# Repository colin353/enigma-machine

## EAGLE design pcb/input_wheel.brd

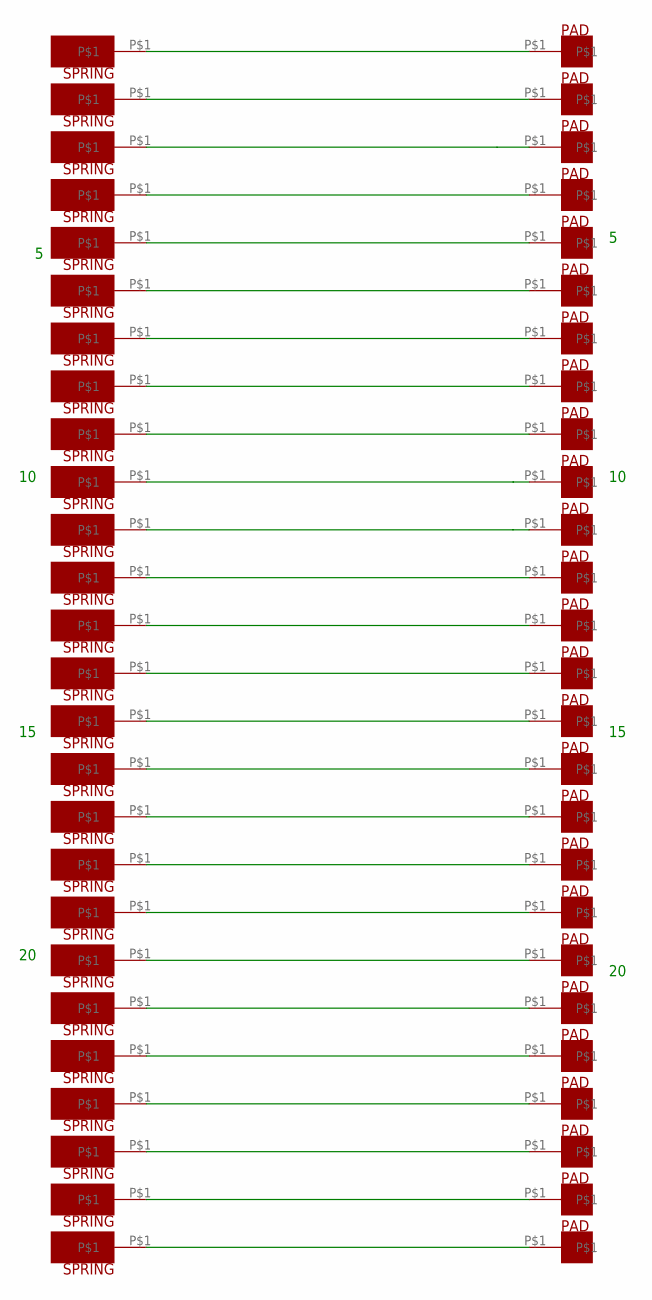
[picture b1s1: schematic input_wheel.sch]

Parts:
U$1, U$2, U$3, U$4, U$5, U$6, U$7, U$8, U$9, U$10, U$11, U$12, U$13, U$14, U$15, U$16, U$17, U$18, U$19, U$20, U$21, U$22, U$23, U$24, U$25, U$26: CONTACT
U$27, U$28, U$29, U$30, U$31, U$32, U$33, U$34, U$35, U$36, U$37, U$38, U$39, U$40, U$41, U$42, U$43, U$44, U$45, U$46, U$47, U$48, U$49, U$50, U$51, U$52: SPRING

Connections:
unnamed: U$10.P$1, U$36.P$1
unnamed: U$1.P$1, U$27.P$1
unnamed: U$2.P$1, U$28.P$1
unnamed: U$4.P$1, U$30.P$1
unnamed: U$11.P$1, U$37.P$1
unnamed: U$5.P$1, U$31.P$1
unnamed: U$6.P$1, U$32.P$1
unnamed: U$7.P$1, U$33.P$1
unnamed: U$8.P$1, U$34.P$1
unnamed: U$9.P$1, U$35.P$1
unnamed: U$12.P$1, U$38.P$1
unnamed: U$13.P$1, U$39.P$1
unnamed: U$14.P$1, U$40.P$1
unnamed: U$15.P$1, U$41.P$1
unnamed: U$16.P$1, U$42.P$1
unnamed: U$17.P$1, U$43.P$1
unnamed: U$18.P$1, U$44.P$1
unnamed: U$19.P$1, U$45.P$1
unnamed: U$20.P$1, U$46.P$1
unnamed: U$21.P$1, U$47.P$1
unnamed: U$22.P$1, U$48.P$1
unnamed: U$23.P$1, U$49.P$1
unnamed: U$24.P$1, U$50.P$1
unnamed: U$25.P$1, U$51.P$1
unnamed: U$26.P$1, U$52.P$1
unnamed: U$3.P$1, U$29.P$1

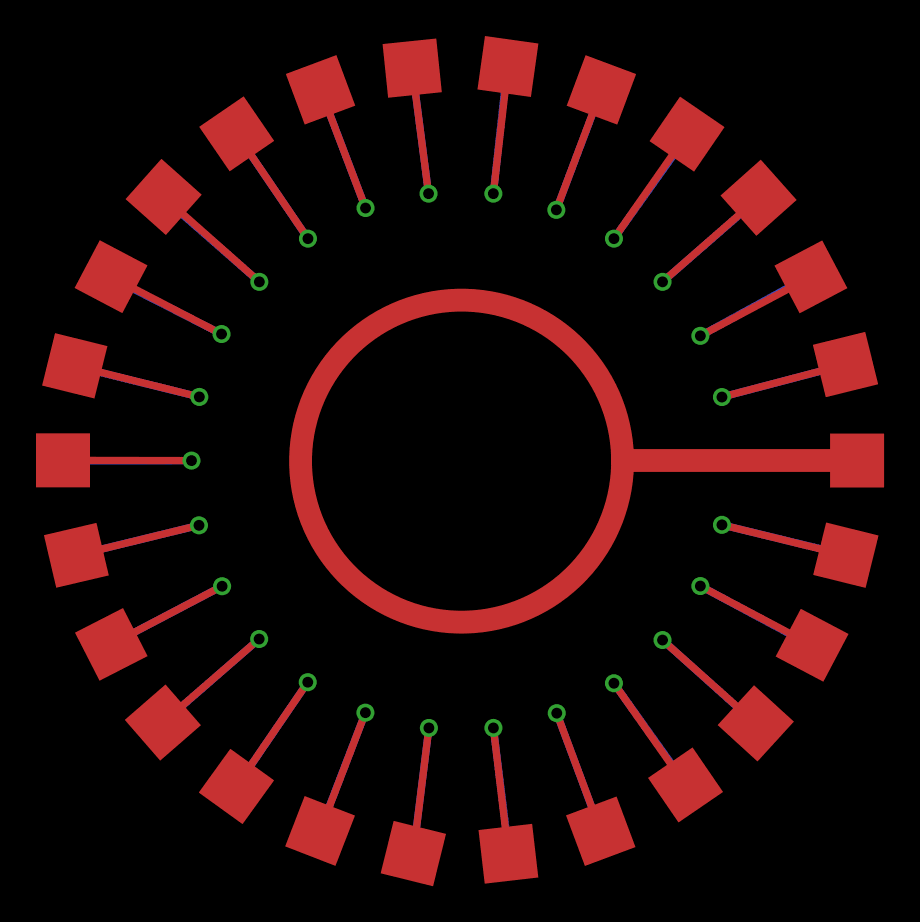
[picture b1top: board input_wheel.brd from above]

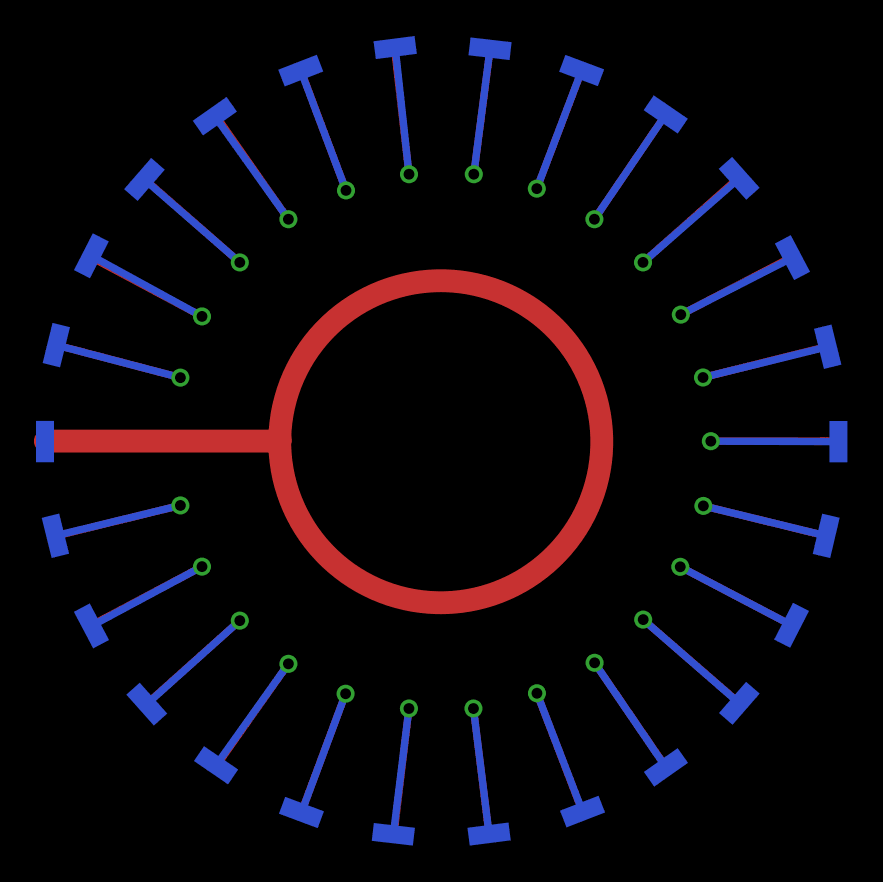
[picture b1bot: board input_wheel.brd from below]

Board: 2 copper layers, 52 parts (26 on the bottom side), 26 nets.

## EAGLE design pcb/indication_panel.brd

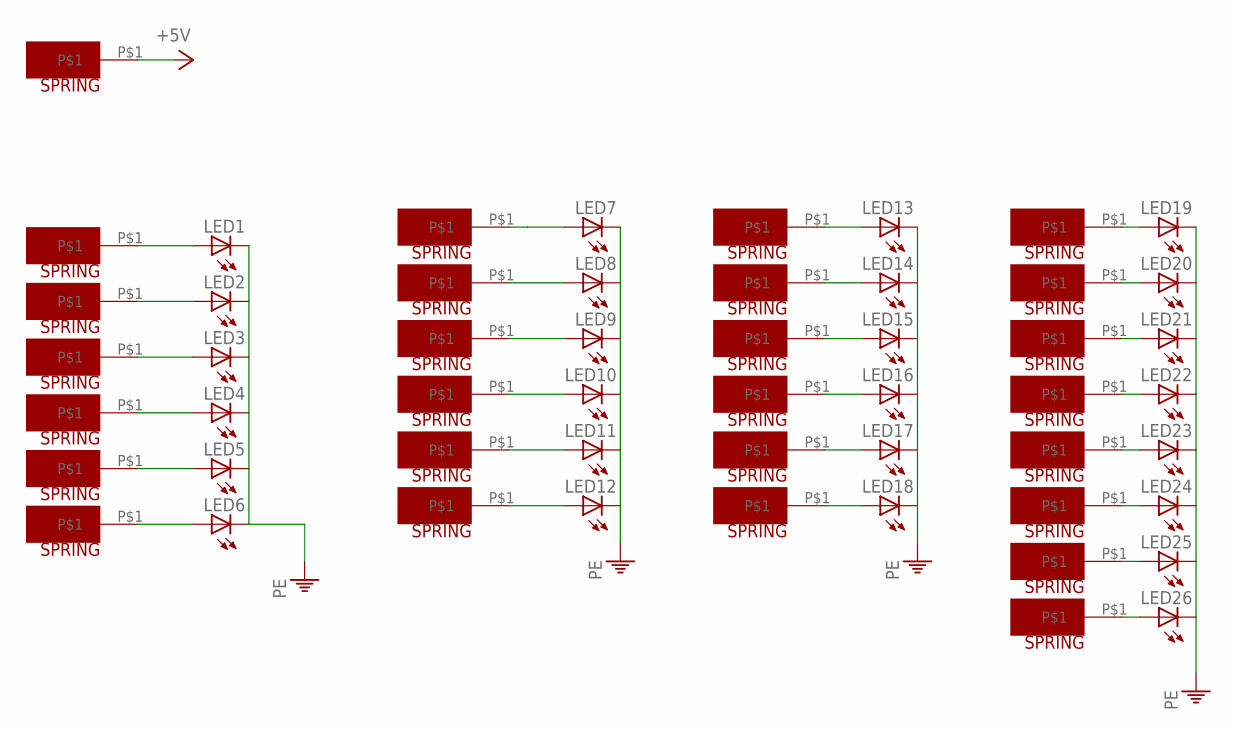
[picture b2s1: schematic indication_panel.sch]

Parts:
+5V: SPRING
LED1, LED2, LED3, LED4, LED5, LED6, LED7, LED8, LED9, LED10, LED11, LED12, LED13, LED14, LED15, LED16, LED17, LED18, LED19, LED20, LED21, LED22, LED23, LED24, LED25, LED26: LEDCHIPLED_0805; CHIPLED_0805
U$1, U$2, U$3, U$4, U$6, U$7, U$8, U$9, U$10, U$11, U$12, U$13, U$14, U$15, U$16, U$17, U$18, U$19, U$20, U$21, U$22, U$23, U$24, U$25, U$26, U$27: SPRING

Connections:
+5V: U$27.P$1
unnamed: LED1.A, U$1.P$1
unnamed: LED2.A, U$2.P$1
unnamed: LED3.A, U$3.P$1
unnamed: LED4.A, U$4.P$1
unnamed: +5V.P$1, LED5.A
unnamed: LED6.A, U$6.P$1
unnamed: LED7.A, U$7.P$1
unnamed: LED8.A, U$8.P$1
unnamed: LED9.A, U$9.P$1
unnamed: LED10.A, U$10.P$1
unnamed: LED11.A, U$11.P$1
unnamed: LED12.A, U$12.P$1
unnamed: LED13.A, U$19.P$1
unnamed: LED24.A, U$18.P$1
unnamed: LED14.A, U$20.P$1
unnamed: LED15.A, U$21.P$1
unnamed: LED16.A, U$22.P$1
unnamed: LED17.A, U$23.P$1
unnamed: LED18.A, U$24.P$1
unnamed: LED19.A, U$13.P$1
unnamed: LED20.A, U$14.P$1
unnamed: LED21.A, U$15.P$1
unnamed: LED22.A, U$16.P$1
unnamed: LED23.A, U$17.P$1
unnamed: LED25.A, U$25.P$1
unnamed: LED26.A, U$26.P$1
PE: LED1.C, LED2.C, LED3.C, LED4.C, LED5.C, LED6.C, LED7.C, LED8.C, LED9.C, LED10.C, LED11.C, LED12.C, LED13.C, LED14.C, LED15.C, LED16.C, LED17.C, LED18.C, LED19.C, LED20.C, LED21.C, LED22.C, LED23.C, LED24.C, LED25.C, LED26.C

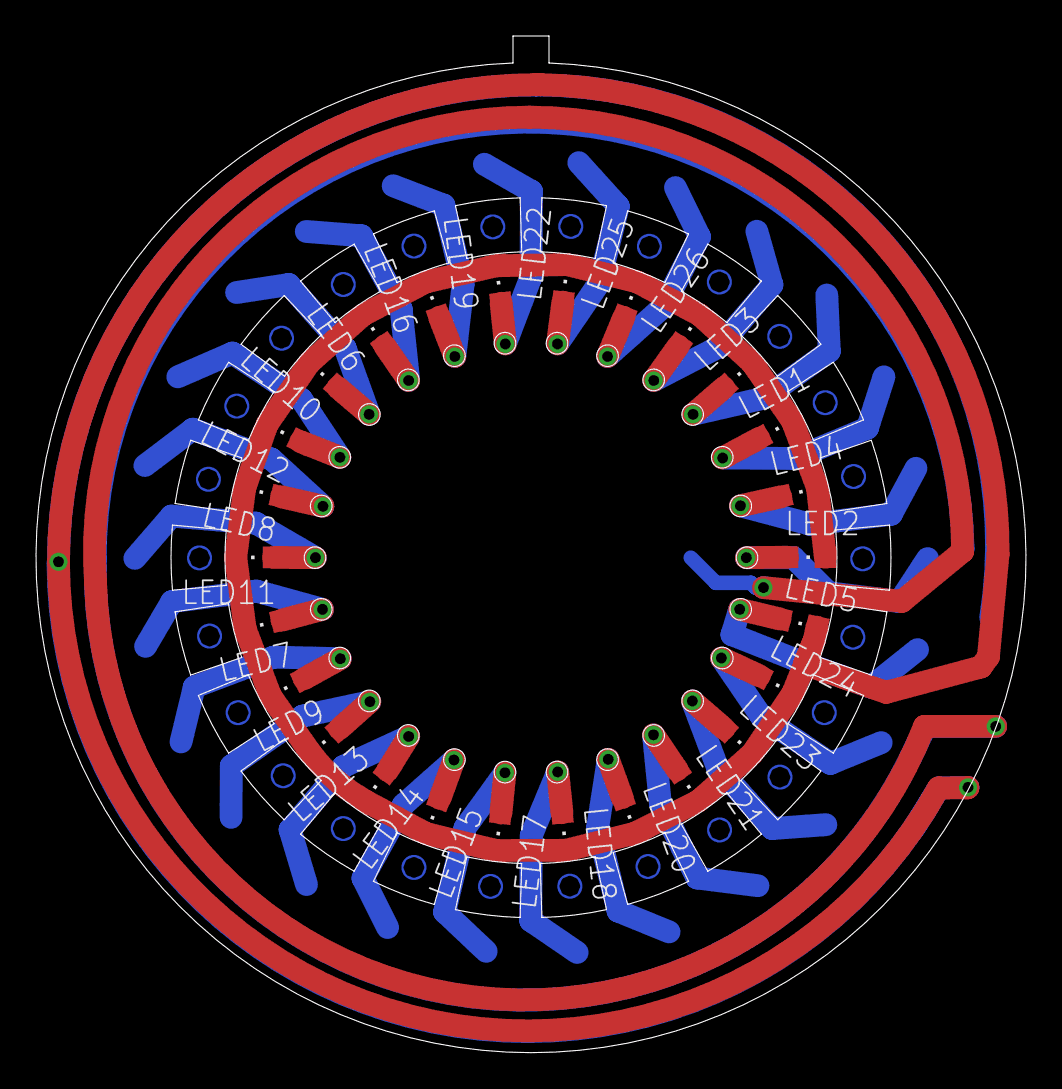
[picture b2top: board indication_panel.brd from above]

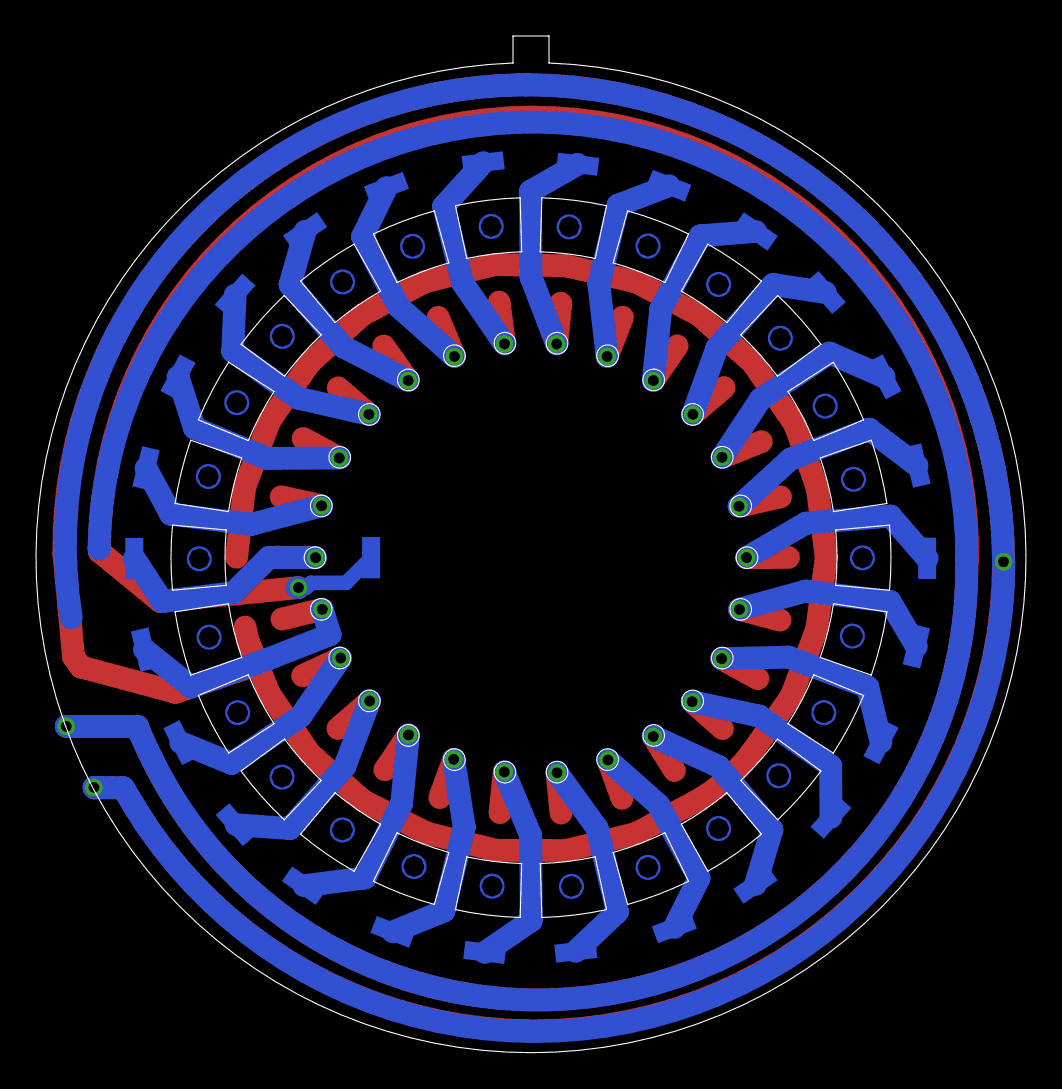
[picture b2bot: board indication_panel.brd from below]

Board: 2 copper layers, 55.0 x 56.5 mm, 53 parts (27 on the bottom side), 27 nets.

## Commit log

2014-03-02 First commit
    Enigma machine replica, at least in spirit. Files are a mess right now,
    will fix them up later.
2015-05-10 Removed old files, replaced with new stuff
2015-05-10 Updated gitgnore, added screenshots
2015-05-17 Many updates
    - Scambler gear assembly
    - End cap gear assembly
    - Gear drawings
    - Much progress on the total assembly
2015-05-17 Plunger updated, spring added
2015-05-18 Significant updates
    - indication pcb updates
    - enclosure updates
2015-07-04 Ready to test 3D print gear wheels
2015-07-09 New parts, fixed assembly
2015-07-14 3D assembly done
2015-08-03 Added circuit board filse
2016-03-15 Update to new SW version
